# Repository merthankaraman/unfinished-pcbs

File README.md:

# unfinished-pcbs
This repo contains my unfinished PCB designs.

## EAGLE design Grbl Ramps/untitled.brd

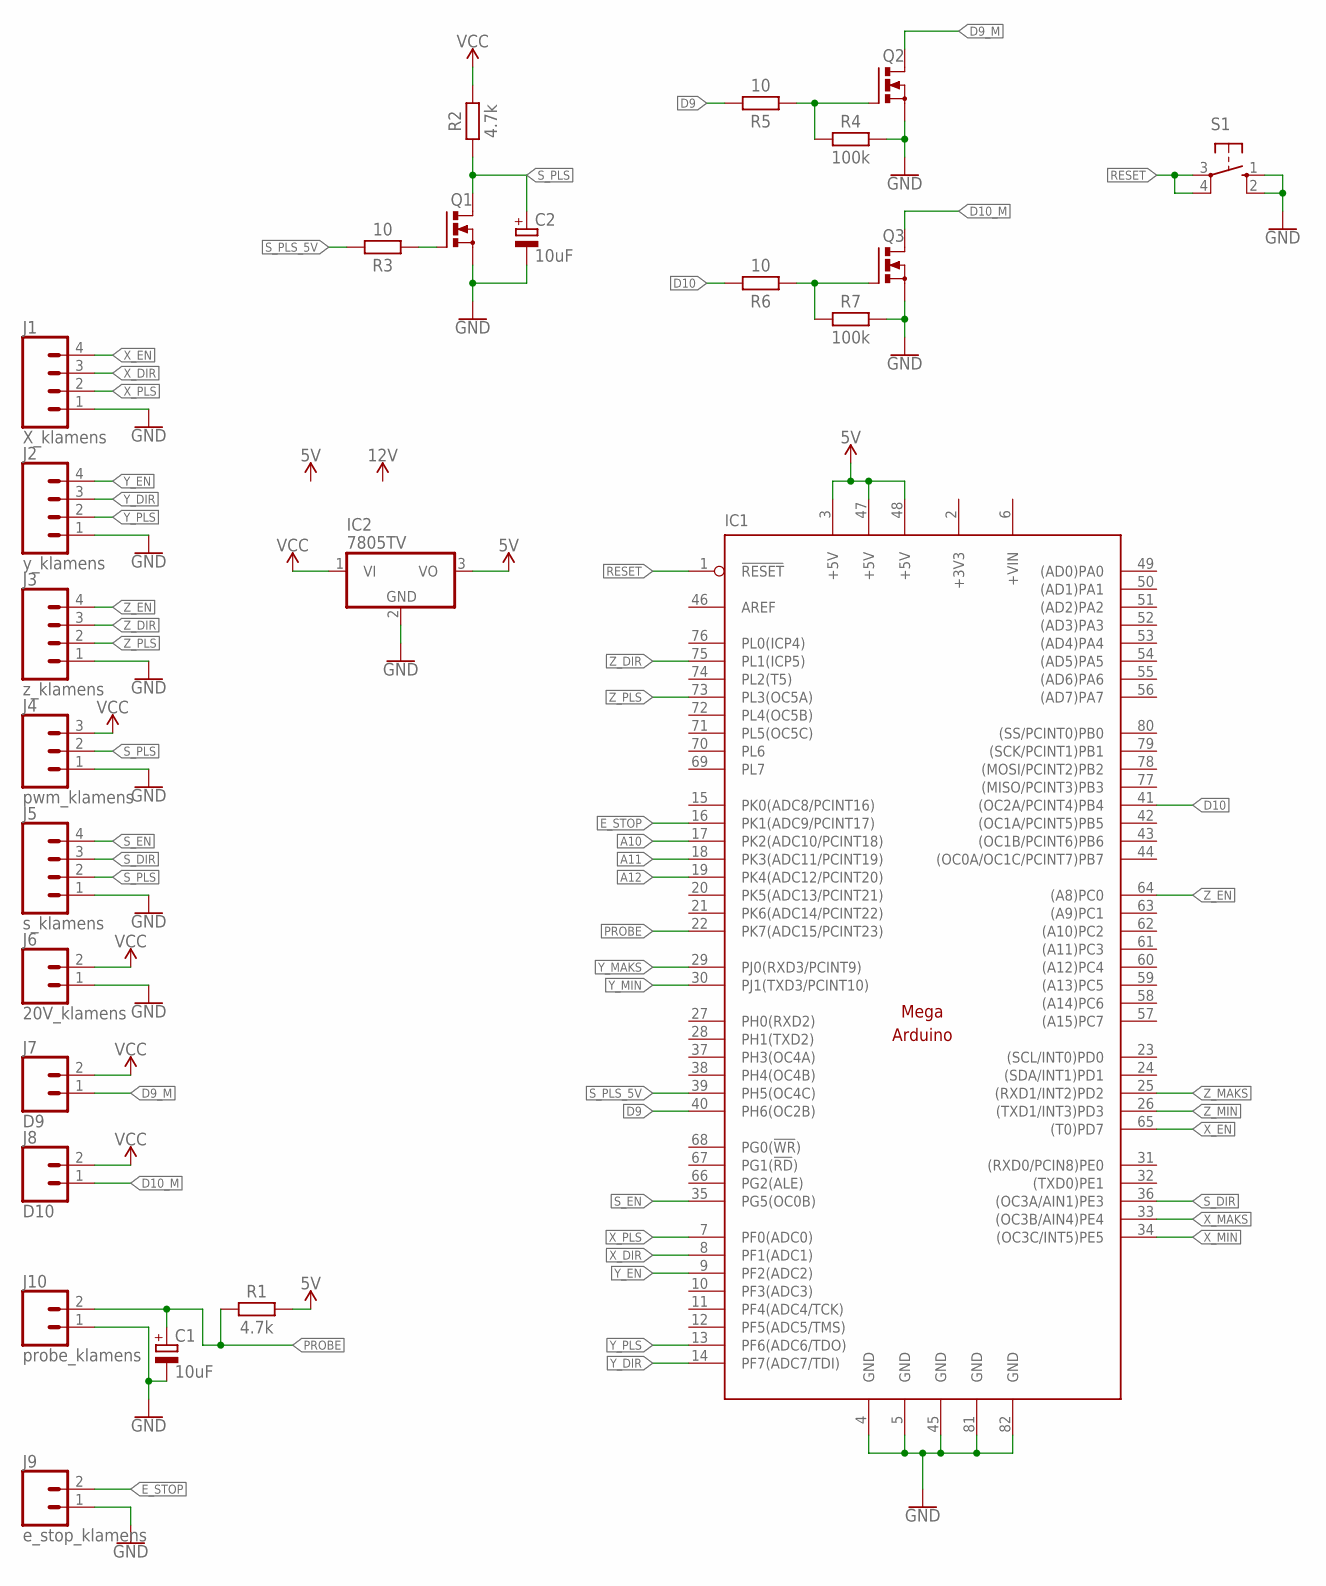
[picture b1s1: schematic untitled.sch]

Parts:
C1, C2: 10uF; CAPPRD508W65D1000H1100B
IC1: MEGAARDUINO_1; MEGA_ARDUINO
IC2: 7805TV; TO220V
J1: X_klamens; SCREWTERMINAL-3.5MM-4_LOCK
J2: y_klamens; SCREWTERMINAL-3.5MM-4_LOCK
J3: z_klamens; SCREWTERMINAL-3.5MM-4_LOCK
J4: pwm_klamens; SCREWTERMINAL-3.5MM-3
J5: s_klamens; SCREWTERMINAL-3.5MM-4_LOCK
J6: 20V_klamens; SCREWTERMINAL-3.5MM-2_LOCK
J7: D9; SCREWTERMINAL-3.5MM-2_LOCK
J8: D10; SCREWTERMINAL-3.5MM-2_LOCK
J9: e_stop_klamens; SCREWTERMINAL-3.5MM-2_LOCK
J10: probe_klamens; SCREWTERMINAL-3.5MM-2_LOCK
Q1, Q2, Q3: PMOSFET_NTO220BV; TO220BV
R1, R2: 4.7k; RESAD1176W63L850D250B
R3, R5, R6: 10; RESAD1176W63L850D250B
R4, R7: 100k; RESAD1176W63L850D250B
S1: 10-XX; B3F-10XX

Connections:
5V: IC1.3 (+5V), IC1.47 (+5V), IC1.48 (+5V), IC2.3 (VO), R1.2
+3V3: IC1.2 (+3V3)
+VIN: IC1.6 (+VIN)
A10: IC1.17 (PK2(ADC10/PCINT18))
A11: IC1.18 (PK3(ADC11/PCINT19))
A12: IC1.19 (PK4(ADC12/PCINT20))
D9: IC1.40 (PH6(OC2B)), R5.2
D9_M: J7.1, Q2.D
D10: IC1.41 ((OC2A/PCINT4)PB4), R6.2
D10_M: J8.1, Q3.D
E_STOP: IC1.16 (PK1(ADC9/PCINT17)), J9.2
GND: C1.2 (-), C2.2 (-), IC1.4 (GND), IC1.5 (GND), IC1.45 (GND), IC1.81 (GND), IC1.82 (GND), IC2.2 (GND), J1.1, J2.1, J3.1, J4.1, J5.1, J6.1, J9.1, J10.1, Q1.S, Q2.S, Q3.S, R4.2, R7.2, S1.1 (S), S1.2 (S1)
unnamed: Q2.G, R4.1, R5.1
unnamed: Q1.G, R3.1
unnamed: Q3.G, R6.1, R7.1
PROBE: C1.1 (+), IC1.22 (PK7(ADC15/PCINT23)), J10.2, R1.1
RESET: IC1.1 (!RESET), S1.3, S1.4 (P1)
S_DIR: IC1.36 ((OC3A/AIN1)PE3), J5.3
S_EN: IC1.35 (PG5(OC0B)), J5.4
S_PLS: C2.1 (+), J4.2, J5.2, Q1.D, R2.1
S_PLS_5V: IC1.39 (PH5(OC4C)), R3.2
VCC: IC2.1 (VI), J4.3, J6.2, J7.2, J8.2, R2.2
X_DIR: IC1.8 (PF1(ADC1)), J1.3
X_EN: IC1.65 ((T0)PD7), J1.4
X_MAKS: IC1.33 ((OC3B/AIN4)PE4)
X_MIN: IC1.34 ((OC3C/INT5)PE5)
X_PLS: IC1.7 (PF0(ADC0)), J1.2
Y_DIR: IC1.14 (PF7(ADC7/TDI)), J2.3
Y_EN: IC1.9 (PF2(ADC2)), J2.4
Y_MAKS: IC1.29 (PJ0(RXD3/PCINT9))
Y_MIN: IC1.30 (PJ1(TXD3/PCINT10))
Y_PLS: IC1.13 (PF6(ADC6/TDO)), J2.2
Z_DIR: IC1.75 (PL1(ICP5)), J3.3
Z_EN: IC1.64 ((A8)PC0), J3.4
Z_MAKS: IC1.25 ((RXD1/INT2)PD2)
Z_MIN: IC1.26 ((TXD1/INT3)PD3)
Z_PLS: IC1.73 (PL3(OC5A)), J3.2

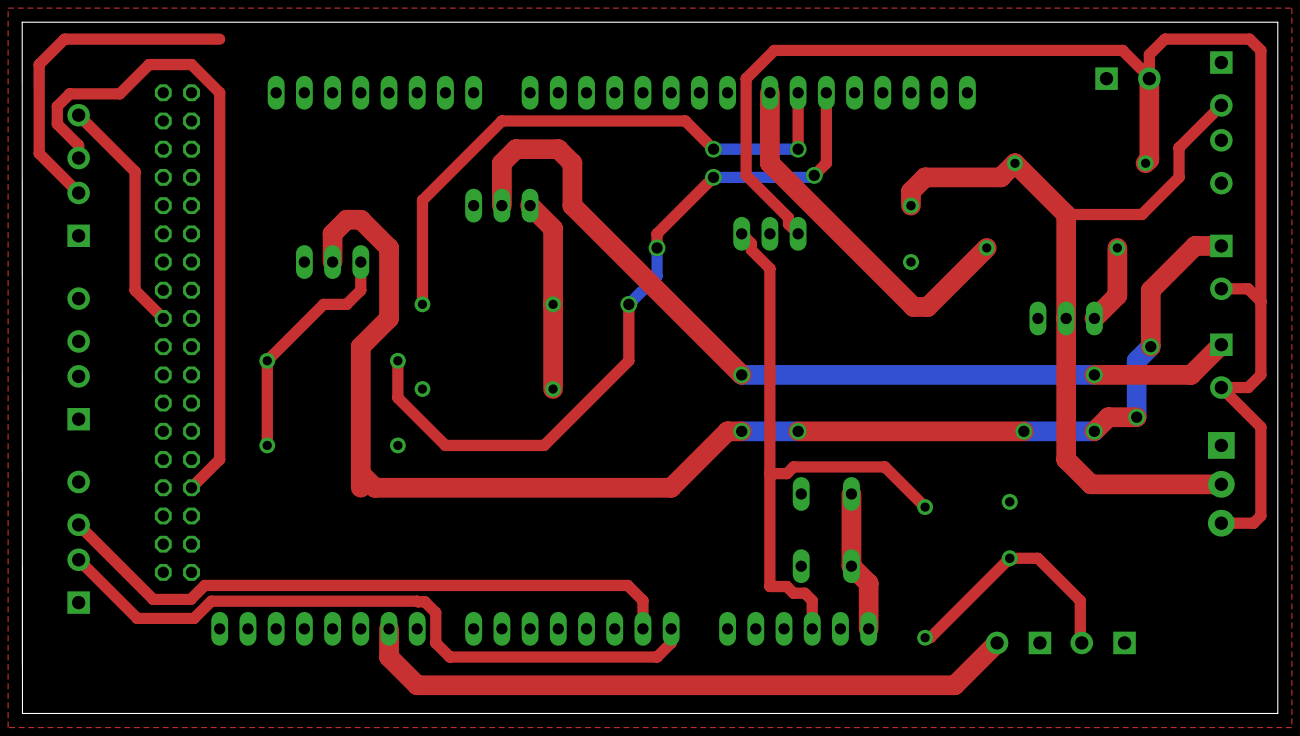
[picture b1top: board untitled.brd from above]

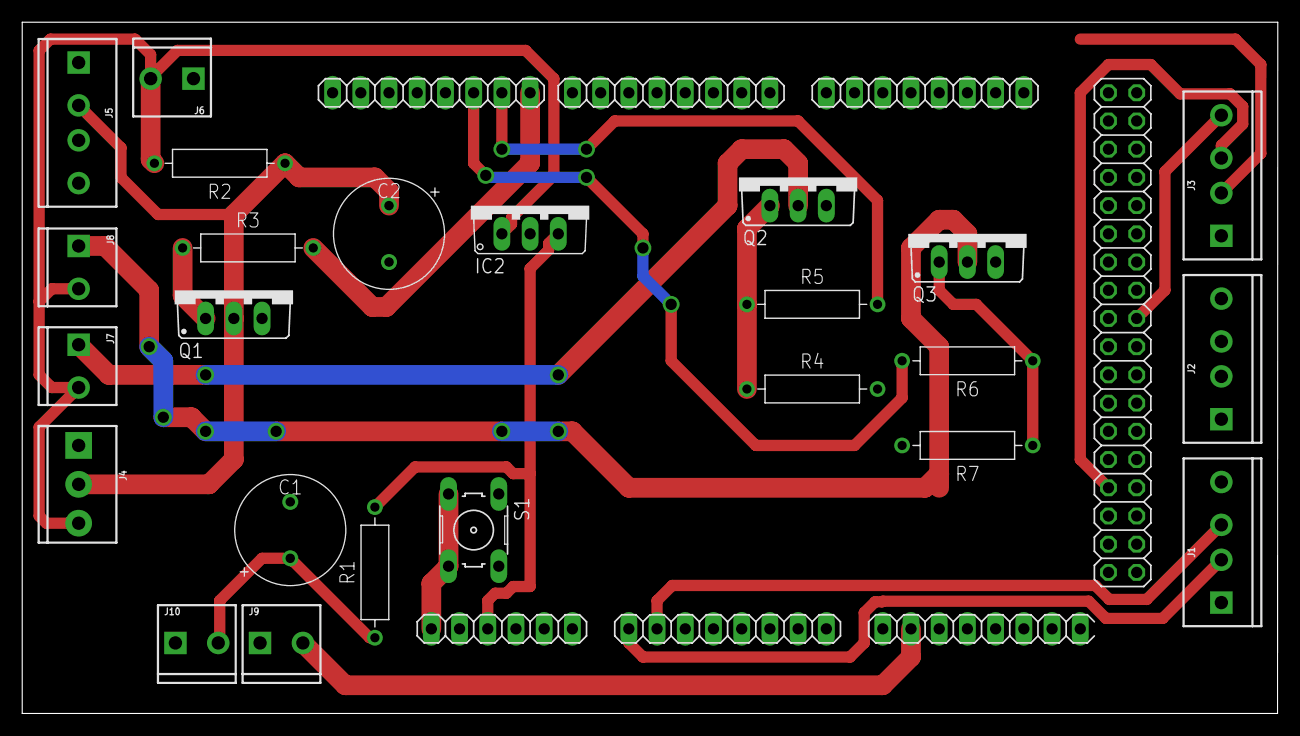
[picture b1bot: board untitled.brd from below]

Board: 2 copper layers, 113.0 x 62.2 mm, 25 parts (25 on the bottom side), 26 nets.

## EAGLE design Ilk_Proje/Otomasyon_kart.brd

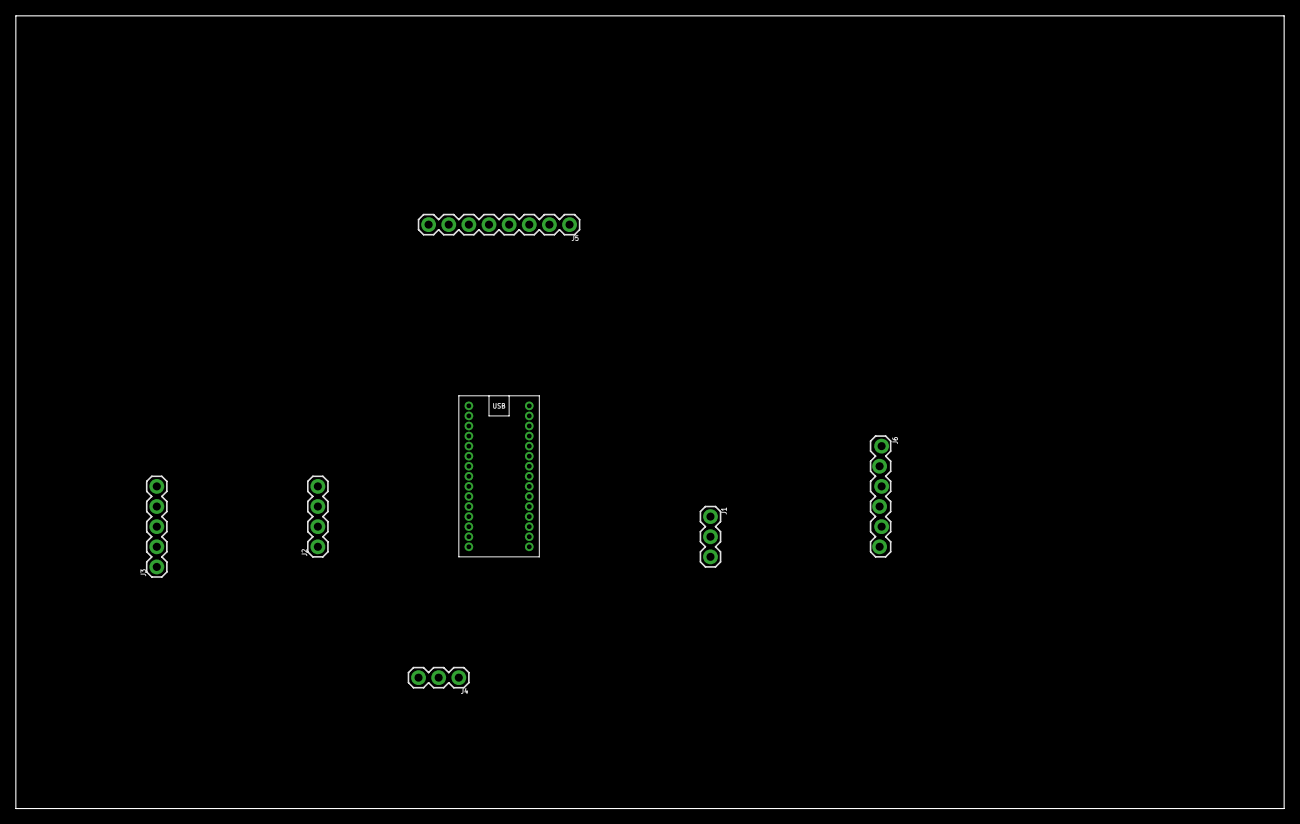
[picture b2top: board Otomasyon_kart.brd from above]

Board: 2 copper layers, 160.0 x 100.0 mm, 7 parts (0 on the bottom side), 15 nets, no tracks yet.

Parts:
J1, J4: 1X03
J2: 1X04
J3: 1X05
J5: 1X08
J6: 1X06_LOCK
U$1: ARDUINO_NANO

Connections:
3V3: J5.8, U$1.3V3
5V: J1.2, J2.2, J3.1, J4.3, J6.5, U$1.5V@1
BT_RX: J6.3, U$1.D7
BT_TX: J6.2, U$1.D8
EKRAN_SCL: J2.4, U$1.A5
EKRAN_SDA: J2.3, U$1.A4
GND: J1.3, J2.1, J3.5, J4.2, J5.6, J6.4, U$1.GND@1, U$1.GND@2
KART_MISO: J5.4, U$1.D12
KART_MOSI: J5.3, U$1.D11
KART_RST: J5.7, U$1.D9
KART_SCK: J5.2, U$1.D13
KART_SDA: J5.1, U$1.D10
KIZIL_OTESI: J4.1, U$1.D3
POT: J3.3, U$1.A1
ROLE: J1.1, U$1.D2

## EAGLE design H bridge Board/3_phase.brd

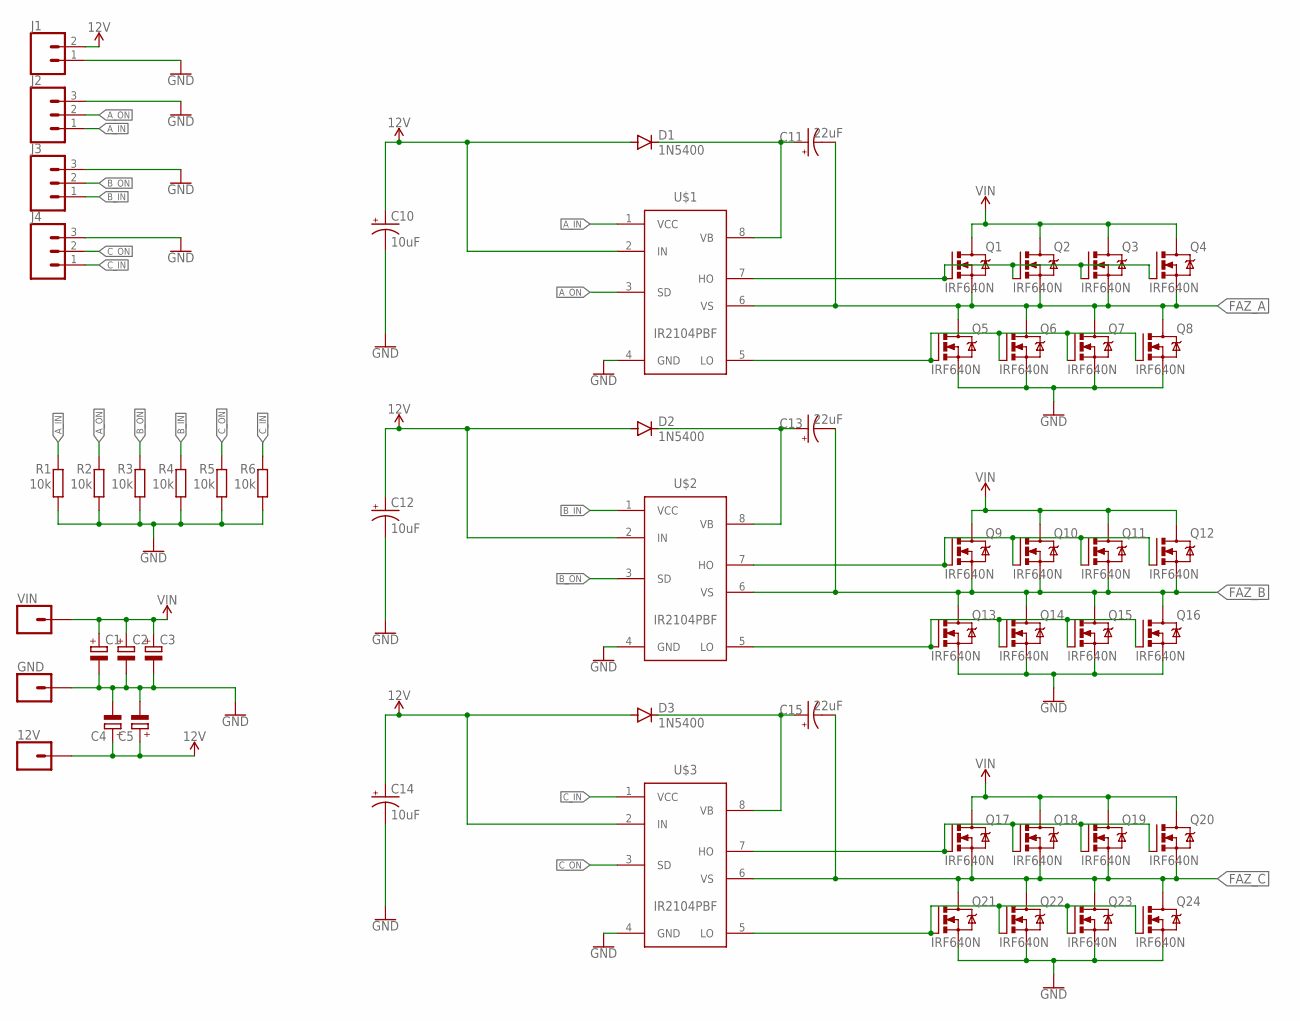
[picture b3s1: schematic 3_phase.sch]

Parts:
12V: CONN_01SNAP-MALE; SNAP-MALE
C1, C2, C3, C4, C5: 16MM-DIA-CAPASITOR
C10, C12, C14: 10uF; CPOL-RADIAL-2.5MM-5MM
C11, C13, C15: 22uF; CPOL-RADIAL-2.5MM-5MM
D1, D2, D3: 1N5400; DO201-15
GND: CONN_01SNAP-MALE; SNAP-MALE
J1: CONN_025MM; SCREWTERMINAL-5MM-2
J2, J3, J4: CONN_03-SCREW-5MM; SCREWTERMINAL-5MM-3
Q1, Q2, Q3, Q4, Q5, Q6, Q7, Q8, Q9, Q10, Q11, Q12, Q13, Q14, Q15, Q16, Q17, Q18, Q19, Q20, Q21, Q22, Q23, Q24: IRF640N; TO-220-PAD
R1, R2, R3, R4, R5, R6: 10k; 0207/10
U$1, U$2, U$3: IR2104PBF; DIP-8
VIN: CONN_01SNAP-MALE; SNAP-MALE

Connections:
12V: 12V.2, C4.+, C5.+, C10.1 (+), C12.1 (+), C14.1 (+), D1.A, D2.A, D3.A, J1.2, U$1.2 (IN), U$2.2 (IN), U$3.2 (IN)
A_IN: J2.1, R1.2, U$1.1 (VCC)
A_ON: J2.2, R2.2, U$1.3 (SD)
B_IN: J3.1, R4.2, U$2.1 (VCC)
B_ON: J3.2, R3.2, U$2.3 (SD)
C_IN: J4.1, R6.2, U$3.1 (VCC)
C_ON: J4.2, R5.2, U$3.3 (SD)
FAZ_A: C11.2 (-), Q1.3 (S), Q2.3 (S), Q3.3 (S), Q4.3 (S), Q5.TAB (D), Q6.TAB (D), Q7.TAB (D), Q8.TAB (D), U$1.6 (VS)
FAZ_A_H: Q1.1 (G), Q2.1 (G), Q3.1 (G), Q4.1 (G), U$1.7 (HO)
FAZ_A_L: Q5.1 (G), Q6.1 (G), Q7.1 (G), Q8.1 (G), U$1.5 (LO)
FAZ_B: C13.2 (-), Q9.3 (S), Q10.3 (S), Q11.3 (S), Q12.3 (S), Q13.TAB (D), Q14.TAB (D), Q15.TAB (D), Q16.TAB (D), U$2.6 (VS)
FAZ_B_L: Q13.1 (G), Q14.1 (G), Q15.1 (G), Q16.1 (G), U$2.5 (LO)
FAZ_B_L1: Q21.1 (G), Q22.1 (G), Q23.1 (G), Q24.1 (G), U$3.5 (LO)
FAZ_C: C15.2 (-), Q17.3 (S), Q18.3 (S), Q19.3 (S), Q20.3 (S), Q21.TAB (D), Q22.TAB (D), Q23.TAB (D), Q24.TAB (D), U$3.6 (VS)
FAZ_C_H: Q17.1 (G), Q18.1 (G), Q19.1 (G), Q20.1 (G), U$3.7 (HO)
GND: C1.-, C2.-, C3.-, C4.-, C5.-, C10.2 (-), C12.2 (-), C14.2 (-), GND.2, J1.1, J2.3, J3.3, J4.3, Q5.3 (S), Q6.3 (S), Q7.3 (S), Q8.3 (S), Q13.3 (S), Q14.3 (S), Q15.3 (S), Q16.3 (S), Q21.3 (S), Q22.3 (S), Q23.3 (S), Q24.3 (S), R1.1, R2.1, R3.1, R4.1, R5.1, R6.1, U$1.4 (GND), U$2.4 (GND), U$3.4 (GND)
unnamed: Q9.1 (G), Q10.1 (G), Q11.1 (G), Q12.1 (G), U$2.7 (HO)
unnamed: C11.1 (+), D1.C, U$1.8 (VB)
unnamed: C15.1 (+), D3.C, U$3.8 (VB)
unnamed: C13.1 (+), D2.C, U$2.8 (VB)
VIN: C1.+, C2.+, C3.+, Q1.TAB (D), Q2.TAB (D), Q3.TAB (D), Q4.TAB (D), Q9.TAB (D), Q10.TAB (D), Q11.TAB (D), Q12.TAB (D), Q17.TAB (D), Q18.TAB (D), Q19.TAB (D), Q20.TAB (D), VIN.2

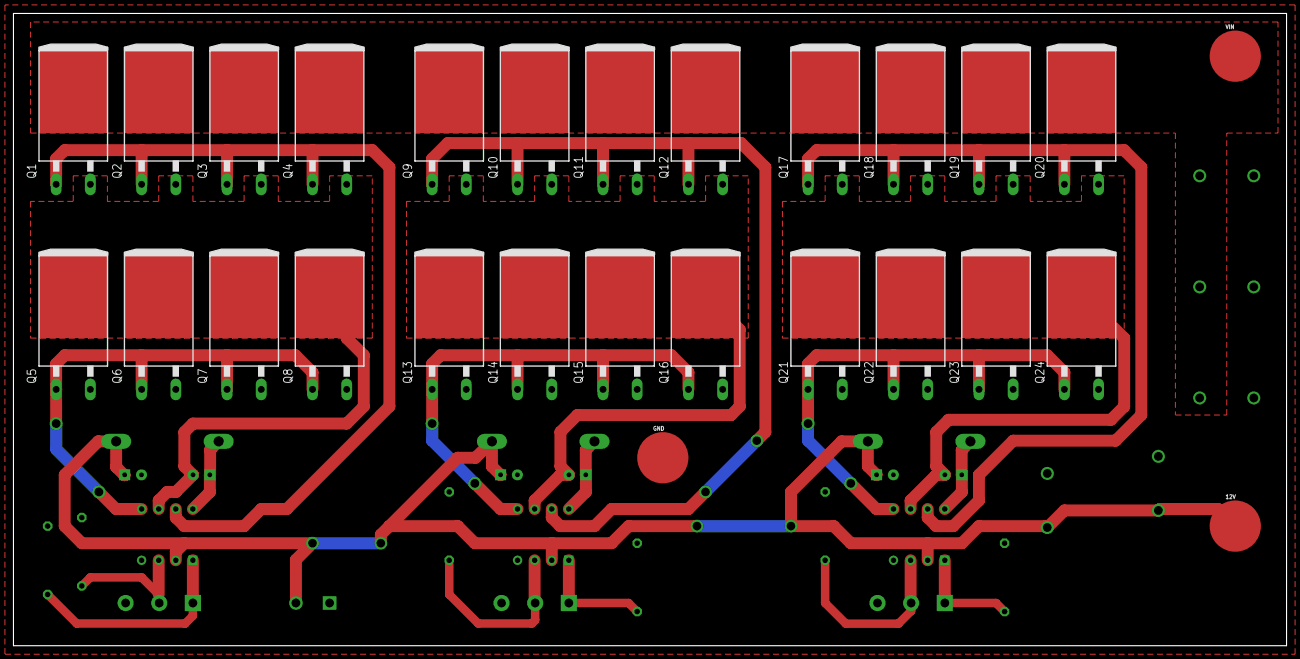
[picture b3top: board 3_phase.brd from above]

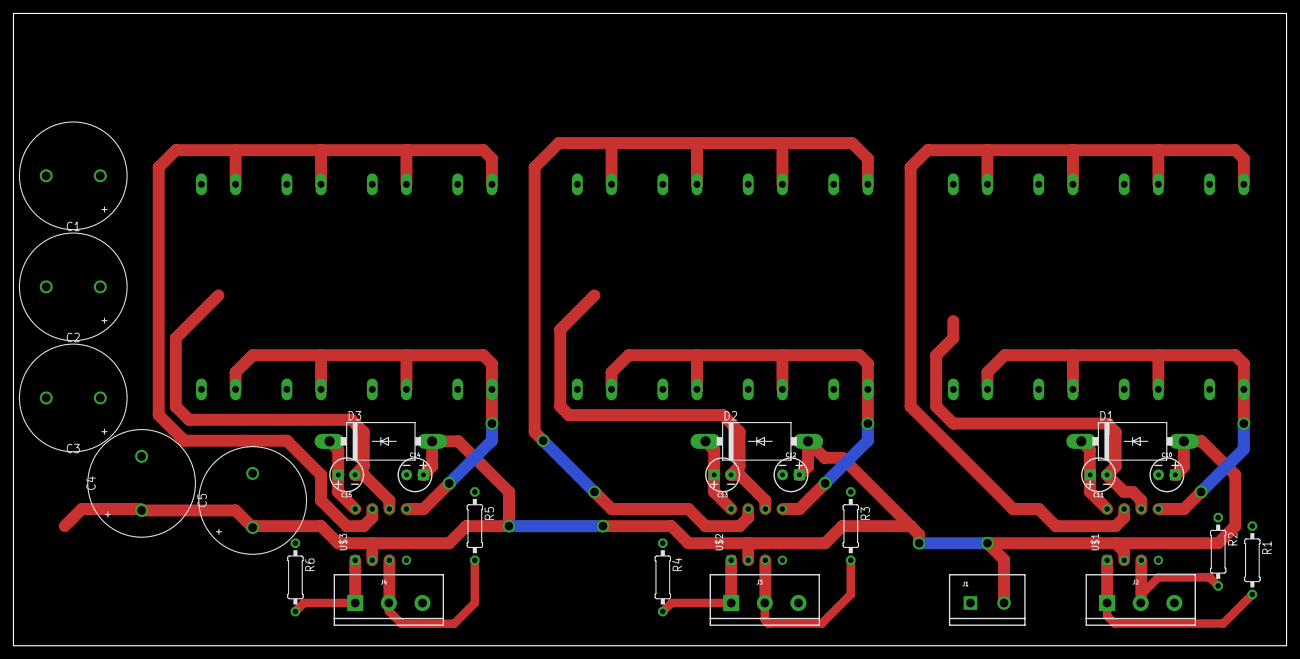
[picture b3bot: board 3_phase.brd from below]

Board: 2 copper layers, 189.2 x 94.0 mm, 54 parts (27 on the bottom side), 21 nets.

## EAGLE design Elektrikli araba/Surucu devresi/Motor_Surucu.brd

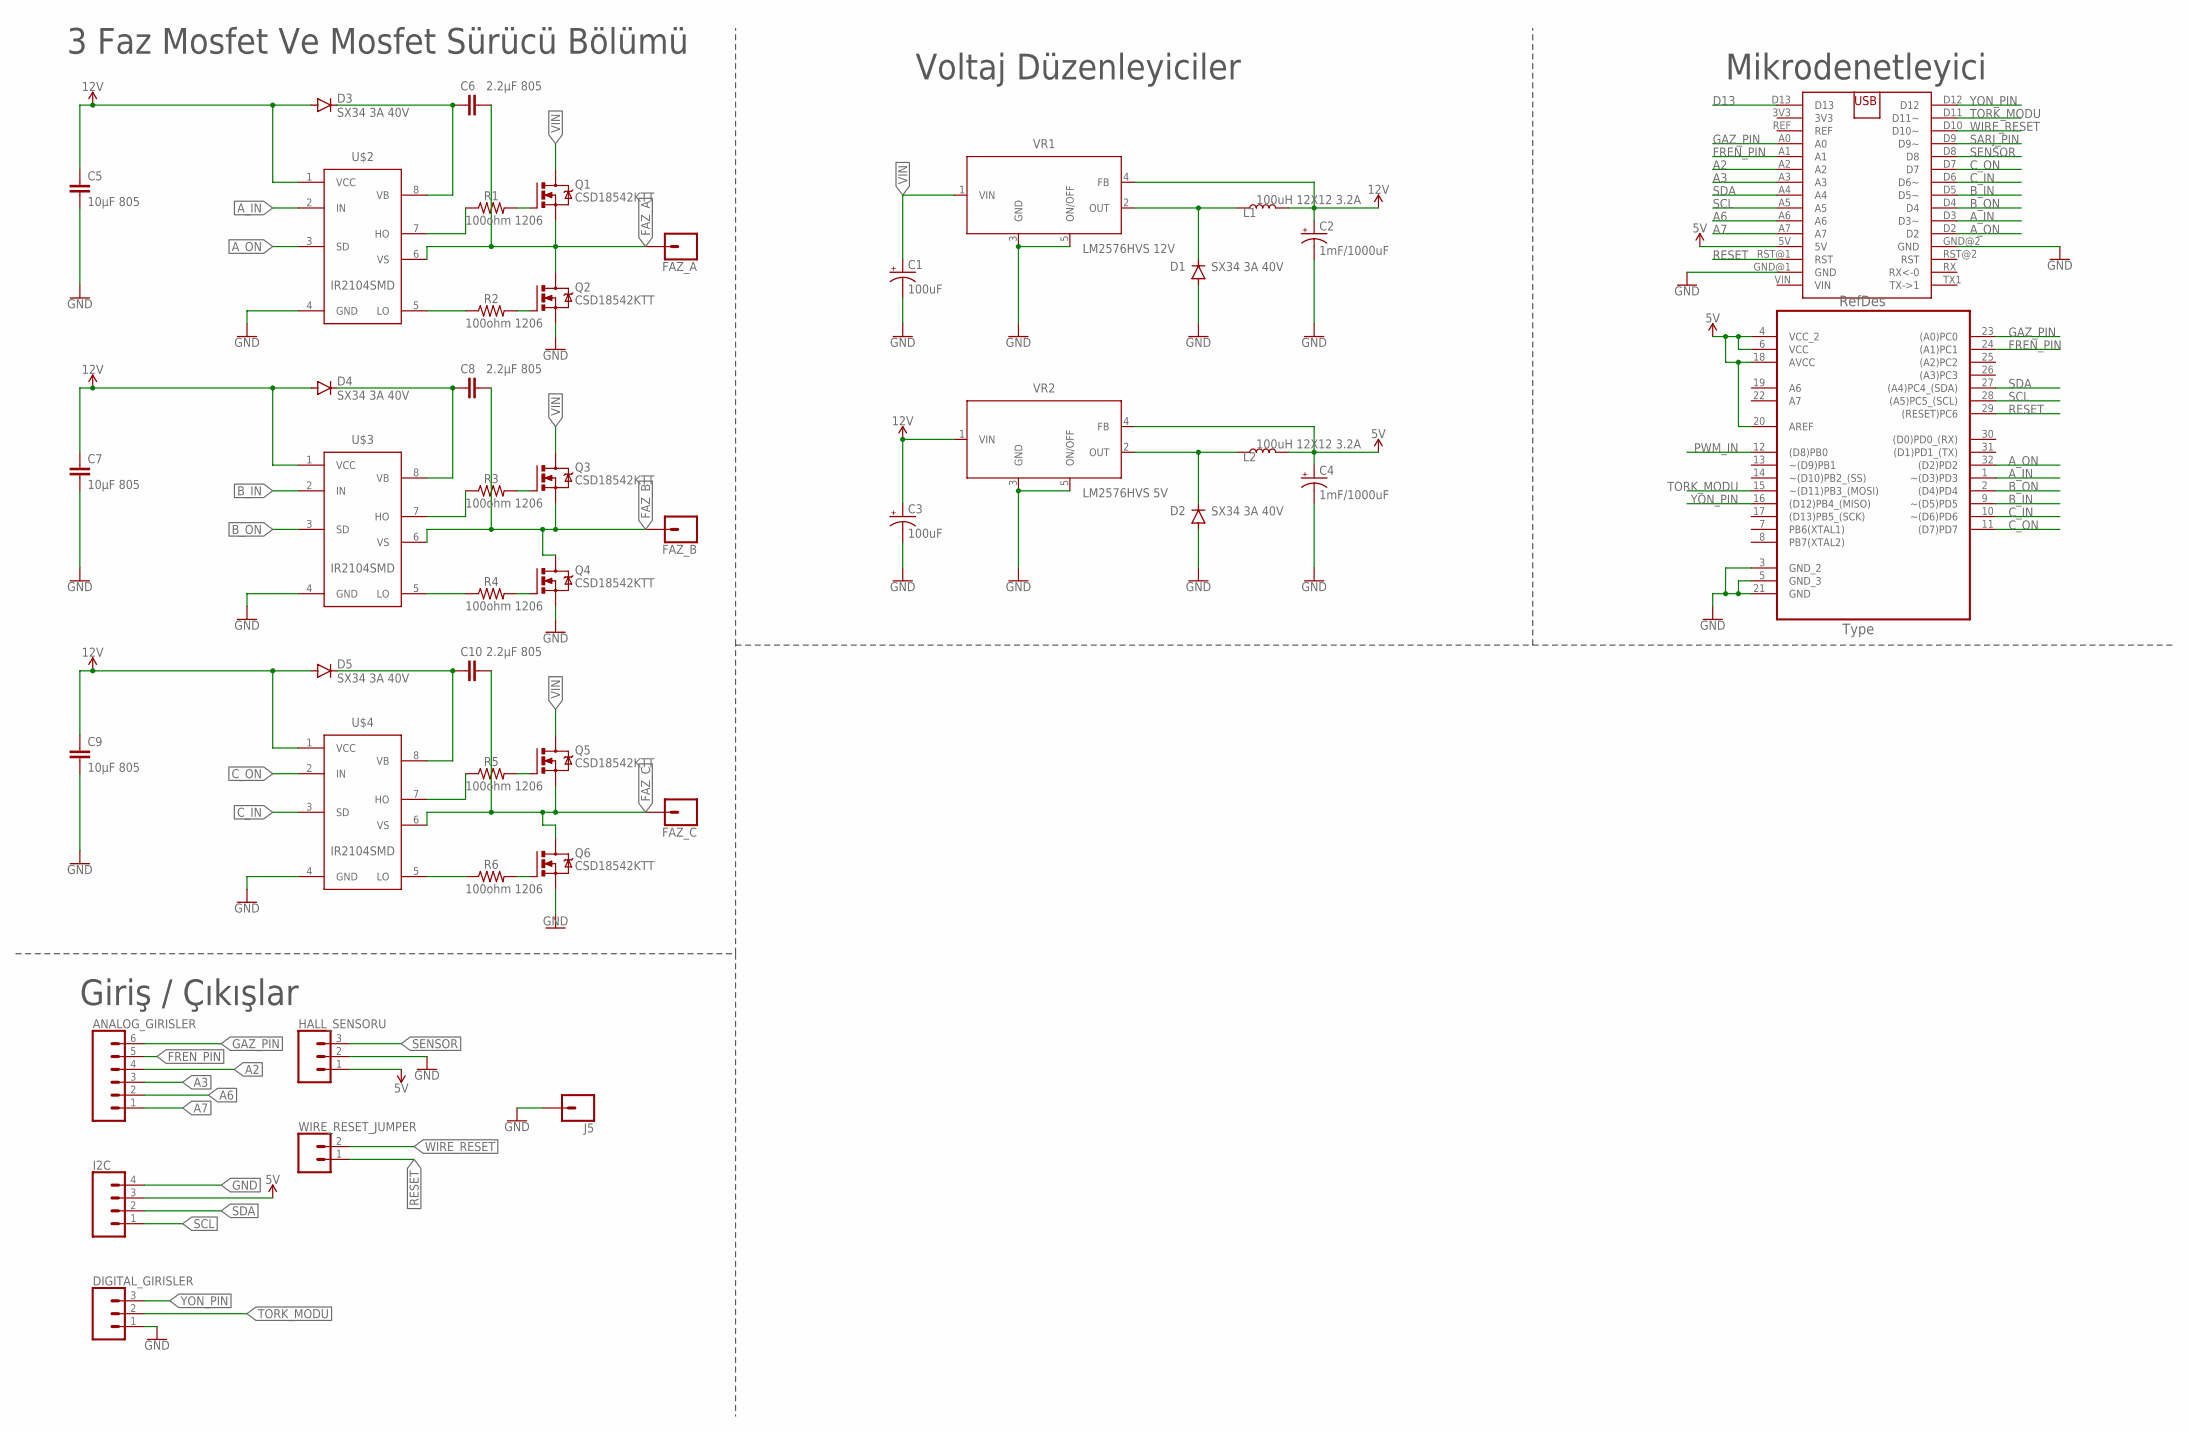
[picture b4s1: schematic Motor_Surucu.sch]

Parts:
ANALOG_GIRISLER: CONN_06LOCK; 1X06_LOCK
C1, C3: 100uF; CPOL-RADIAL-2.5MM-6.5MM
C2, C4: 1mF/1000uF; PANASONIC_G
C5, C7, C9: 10µF 805; 0805
C6, C8, C10: 2.2µF 805; 0805
D1, D2, D3, D4, D5: SX34 3A 40V; DO214AC
DIGITAL_GIRISLER: CONN_03; 1X03
FAZ_A: CONN_01SNAP-MALE; SNAP-MALE
FAZ_B: CONN_01SNAP-MALE; SNAP-MALE
FAZ_C: CONN_01SNAP-MALE; SNAP-MALE
HALL_SENSORU: CONN_03; 1X03
I2C: CONN_04; 1X04
J5: CONN_01SNAP-MALE; SNAP-MALE
L1, L2: 100uH 12X12 3.2A; INDUCTOR_SDR1307
Q1, Q2, Q3, Q4, Q5, Q6: CSD18542KTT; TO263-3
R1, R2, R3, R4, R5, R6: 100ohm 1206; 1206
U1: ATMEGA328P-AU; QFP80P900X900X120-32N
U$1: ARDUINO_NANO
U$2, U$3, U$4: IR2104SMD; SOIC-8
VR1: LM2576HVS 12V; TO170P1435X465-6N
VR2: LM2576HVS 5V; TO170P1435X465-6N
WIRE_RESET_JUMPER: CONN_02; 1X02

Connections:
5V: C4.+, HALL_SENSORU.1, I2C.3, L2.P$2 (2), U1.4 (VCC_2), U1.6 (VCC), U1.18 (AVCC), U1.20 (AREF), U$1.5V, VR2.4 (FB)
12V: C2.+, C3.1 (+), C5.1, C7.1, C9.1, D3.A, D4.A, D5.A, L1.P$2 (2), U$2.1 (VCC), U$3.1 (VCC), U$4.1 (VCC), VR1.4 (FB), VR2.1 (VIN)
A2: ANALOG_GIRISLER.4, U$1.A2
A3: ANALOG_GIRISLER.3, U$1.A3
A6: ANALOG_GIRISLER.2, U$1.A6
A7: ANALOG_GIRISLER.1, U$1.A7
A_IN: U1.1 (~(D3)PD3), U$1.D3 (D3~), U$2.2 (IN)
A_ON: U1.32 ((D2)PD2), U$1.D2, U$2.3 (SD)
B_IN: U1.9 (~(D5)PD5), U$1.D5 (D5~), U$3.2 (IN)
B_ON: U1.2 ((D4)PD4), U$1.D4, U$3.3 (SD)
C_IN: U1.10 (~(D6)PD6), U$1.D6 (D6~), U$4.3 (SD)
C_ON: U1.11 ((D7)PD7), U$1.D7, U$4.2 (IN)
D13: U$1.D13
FAZ_A: C6.2, FAZ_A.2, Q1.3 (S), Q2.TAB (D), U$2.6 (VS)
FAZ_B: C8.2, FAZ_B.2, Q3.3 (S), Q4.TAB (D), U$3.6 (VS)
FAZ_C: C10.2, FAZ_C.2, Q5.3 (S), Q6.TAB (D), U$4.6 (VS)
FREN_PIN: ANALOG_GIRISLER.5, U1.24 ((A1)PC1), U$1.A1
GAZ_PIN: ANALOG_GIRISLER.6, U1.23 ((A0)PC0), U$1.A0
GND: C1.2 (-), C2.-, C3.2 (-), C4.-, C5.2, C7.2, C9.2, D1.A, D2.A, DIGITAL_GIRISLER.1, HALL_SENSORU.2, I2C.4, J5.2, Q2.3 (S), Q4.3 (S), Q6.3 (S), U1.3 (GND_2), U1.5 (GND_3), U1.21 (GND), U$1.GND@1 (GND), U$1.GND@2 (GND), U$2.4 (GND), U$3.4 (GND), U$4.4 (GND), VR1.3 (GND), VR1.5 (ON/OFF), VR2.3 (GND), VR2.5 (ON/OFF)
unnamed: D2.C, L2.P$1 (1), VR2.2 (OUT)
unnamed: C6.1, D3.C, U$2.8 (VB)
unnamed: Q1.1 (G), R1.2
unnamed: R1.1, U$2.7 (HO)
unnamed: Q2.1 (G), R2.2
unnamed: R2.1, U$2.5 (LO)
unnamed: C8.1, D4.C, U$3.8 (VB)
unnamed: Q3.1 (G), R3.2
unnamed: R3.1, U$3.7 (HO)
unnamed: Q4.1 (G), R4.2
unnamed: R4.1, U$3.5 (LO)
unnamed: C10.1, D5.C, U$4.8 (VB)
unnamed: Q5.1 (G), R5.2
unnamed: R5.1, U$4.7 (HO)
unnamed: Q6.1 (G), R6.2
unnamed: R6.1, U$4.5 (LO)
unnamed: D1.C, L1.P$1 (1), VR1.2 (OUT)
PWM_IN: U1.12 ((D8)PB0)
RESET: U1.29 ((RESET)PC6), U$1.RST@1 (RST), WIRE_RESET_JUMPER.1
SARJ_PIN: U$1.D9 (D9~)
SCL: I2C.1, U1.28 ((A5)PC5_(SCL)), U$1.A5
SDA: I2C.2, U1.27 ((A4)PC4_(SDA)), U$1.A4
SENSOR: HALL_SENSORU.3, U$1.D8
TORK_MODU: DIGITAL_GIRISLER.2, U1.15 (~(D11)PB3_(MOSI)), U$1.D11 (D11~)
VIN: C1.1 (+), Q1.TAB (D), Q3.TAB (D), Q5.TAB (D), VR1.1 (VIN)
WIRE_RESET: U$1.D10 (D10~), WIRE_RESET_JUMPER.2
YON_PIN: DIGITAL_GIRISLER.3, U1.16 ((D12)PB4_(MISO)), U$1.D12

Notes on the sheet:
3 Faz Mosfet Ve Mosfet Sürücü Bölümü
Voltaj Düzenleyiciler
Mikrodenetleyici
Giriş / Çıkışlar

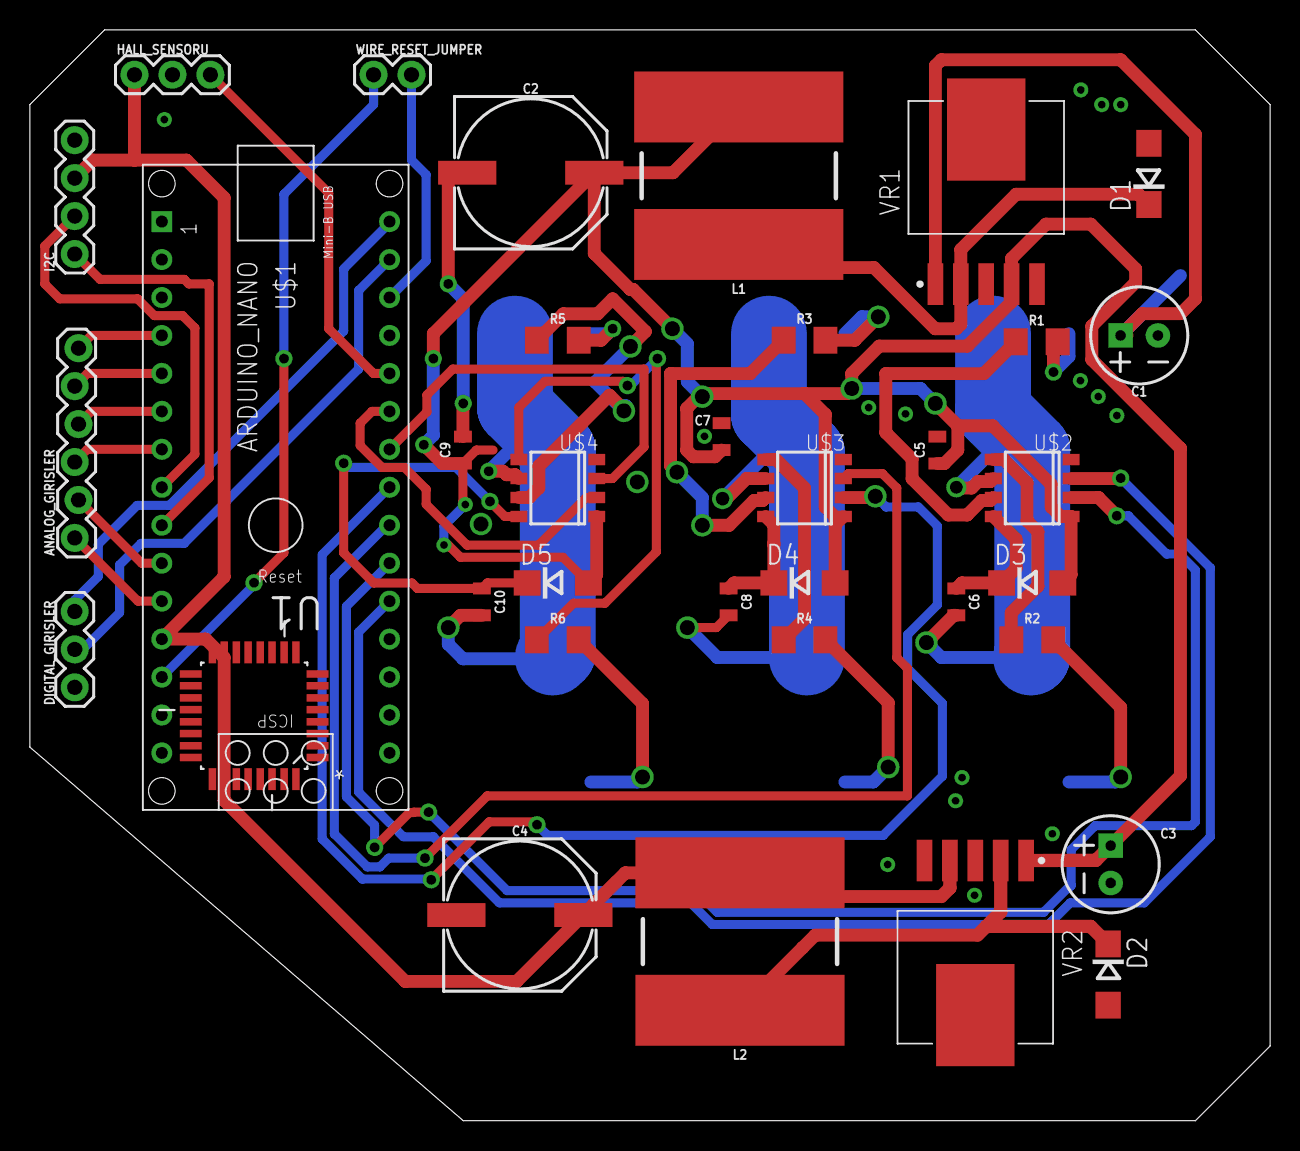
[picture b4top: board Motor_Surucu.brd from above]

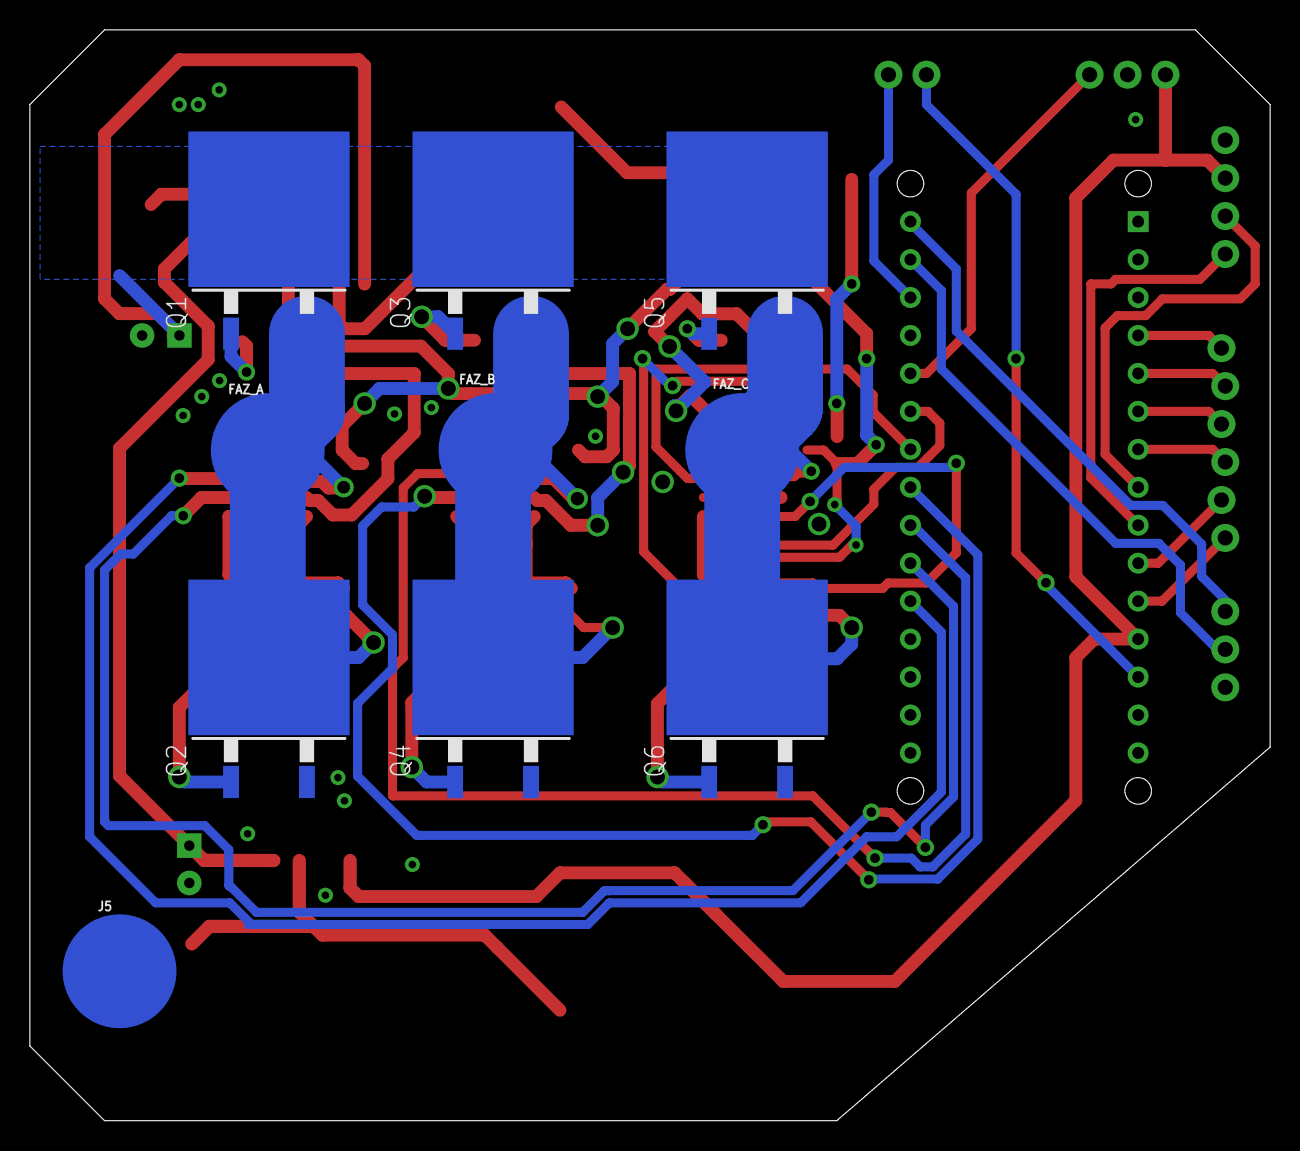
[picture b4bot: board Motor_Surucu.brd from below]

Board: 2 copper layers, 83.0 x 73.0 mm, 45 parts (10 on the bottom side), 43 nets.

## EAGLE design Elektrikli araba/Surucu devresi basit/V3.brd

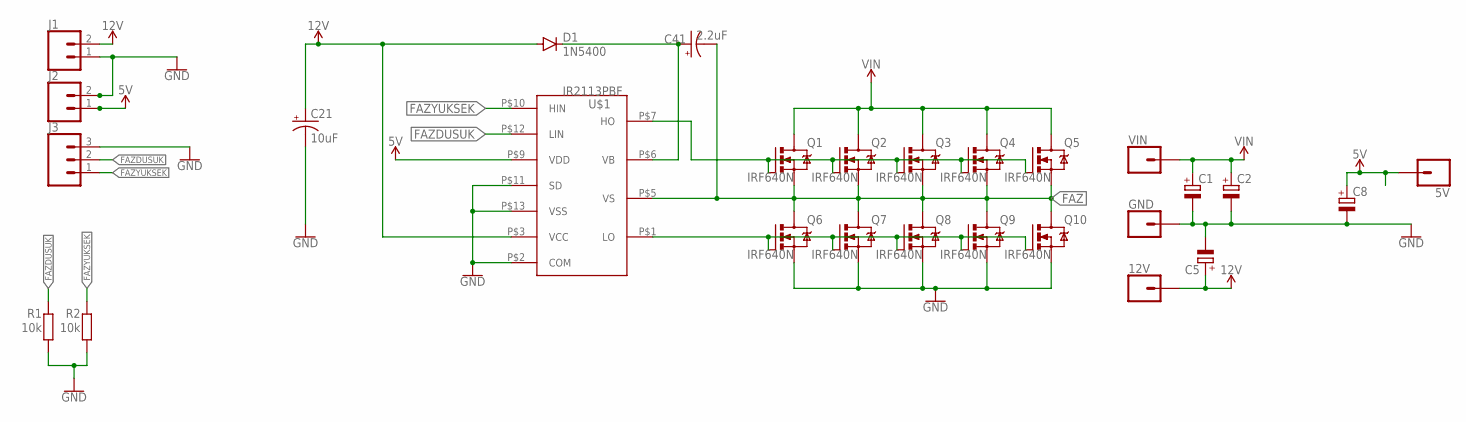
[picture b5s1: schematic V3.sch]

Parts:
5V, 12V: CONN_01SNAP-MALE; SNAP-MALE
C1, C2, C5, C8: 16MM-DIA-CAPASITOR
C21: 10uF; CPOL-RADIAL-2.5MM-5MM
C41: 2.2uF; CPOL-RADIAL-2.5MM-5MM
D1: 1N5400; DO201-15
GND: CONN_01SNAP-MALE; SNAP-MALE
J1, J2: CONN_025MM; SCREWTERMINAL-5MM-2
J3: CONN_03-SCREW-5MM; SCREWTERMINAL-5MM-3
Q1, Q2, Q3, Q4, Q5, Q6, Q7, Q8, Q9, Q10: IRF640N; TO-220-PAD
R1, R2: 10k; 0207/10
U$1: IR2113PBF; PDIP-14
VIN: CONN_01SNAP-MALE; SNAP-MALE

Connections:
5V: 5V.2, C8.+, J2.1, U$1.P$9 (VDD)
12V: 12V.2, C5.+, C21.1 (+), D1.A, J1.2, U$1.P$3 (VCC)
FAZ: C41.2 (-), Q1.3 (S), Q2.3 (S), Q3.3 (S), Q4.3 (S), Q5.3 (S), Q6.TAB (D), Q7.TAB (D), Q8.TAB (D), Q9.TAB (D), Q10.TAB (D), U$1.P$5 (VS)
FAZDUSUK: J3.2, R1.2, U$1.P$12 (LIN)
FAZYUKSEK: J3.1, R2.2, U$1.P$10 (HIN)
FAZ_A_L: Q6.1 (G), Q7.1 (G), Q8.1 (G), Q9.1 (G), Q10.1 (G), U$1.P$1 (LO)
GND: C1.-, C2.-, C5.-, C8.-, C21.2 (-), GND.2, J1.1, J2.2, J3.3, Q6.3 (S), Q7.3 (S), Q8.3 (S), Q9.3 (S), Q10.3 (S), R1.1, R2.1, U$1.P$2 (COM), U$1.P$11 (SD), U$1.P$13 (VSS)
unnamed: Q1.1 (G), Q2.1 (G), Q3.1 (G), Q4.1 (G), Q5.1 (G), U$1.P$7 (HO)
unnamed: C41.1 (+), D1.C, U$1.P$6 (VB)
VIN: C1.+, C2.+, Q1.TAB (D), Q2.TAB (D), Q3.TAB (D), Q4.TAB (D), Q5.TAB (D), VIN.2

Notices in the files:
parts and their libraries:
SparkFun-Connectors: Licensing: Creative Commons ShareAlike 4.0 International - https://creativecommons.org/licenses/by-sa/4.0
